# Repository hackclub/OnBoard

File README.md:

# **<h2>Onboard has ended now :/ <br> But much more to come! Stay tuned :). [Sign up here.](https://forms.hackclub.com/t/xtYYcGvNTCus)<h2>**

# OnBoard - Get a $100 grant and make a PCB!

> "I’m so glad that young people can create things like PC boards online. May your creativity have no limits!”
>
> _– [Steve Wozniak](https://en.wikipedia.org/wiki/Steve_Wozniak), Apple co-founder endorsing Hack Club OnBoard_

It's easier than ever for high school students to get involved with programming; all you need is a computing device and internet access. Yet, *it's not the same for hardware*. While PCB fabs have greatly increased the accessibility for professionally done boards, there is still no clear way for high school students to jump in. This is where OnBoard comes in.

---

Every student will receive up to $100 to cover PCB manufacturing costs, and join a community of peers– some more beginner and some more experienced.

## Requirements

Every design/submission needs to meet the following constraints to be approved:

- Unique and open-source design
- Must be orderable on JLCPCB or other [approved vendor](https://github.com/hackclub/OnBoard/blob/main/docs/VENDORS.md)
- Must be in high school or younger[^1][^2][^3] and show proof of school enrollment to submit

[^1]: Home school still counts!
[^2]: If you left high school early you can also submit.
[^3]: If you need help with ideas for proof of age, ask in our Slack and we'll help you out! [here](https://hackclub.com/slack/?event=onboard)

## Getting Started

> You can also go through a video with instructions on how to submit your grant!
>
> 

### Star the repo (Optional)

To follow the repo for updates and show you're participating, click the "star" button on the [`onboard`](https://github.com/hackclub/OnBoard/) repo.

### 1. Join `#electronics` on Slack!

Our [`#electronics`](https://hackclub.slack.com/archives/C0587U78RK4) channel[^4] is where the party is getting started! If you haven't already joined, make sure to add yourself to the channel. And for those who are new to the Hack Club slack, sign up to our community of 13k+ makers through [here](https://hackclub.com/slack/?event=onboard) (don't worry, there isn't an application).

[^4]: This link only works after you've joined the slack. Make sure to get an invite [here](https://hackclub.com/slack/?event=onboard) first.

Perhaps ping a little hello to `@Kevin Yang`?

### 2. Design a Board!

It's design time! If you've done this before, you can skip ahead to step 3. Most people reading this will be new to PCB design, so we've made a simple tutorial on making an example board.

Check out our [PCB tutorials](https://jams.hackclub.com/tag/pcb), where you'll make a design from scratch in a free online editor. This is jumping in the deep end- it won't explain everything, but it will give you a taste of what's possible. By the end you probably won't understand _what_ you did or _why_ you did it, but you will have a working design for a board and you'll know how to **tweak** and **edit** the design to make it your own.

_If you get stuck on these tutorials, or want more example projects to learn from, post in the Slack channel to hear from others going on their journeys._

### 3. Upload to a Vendor and Take a Screenshot

Upload your Gerber files to [JLCPCB.com](https://jlcpcb.com/) and add them to your cart. JLCPCB is the default PCB manufacturer, but you can shop around [^5] if there's a specific one you want to use [^6]. Ensure you complete the checkout process by entering your address and selecting a shipping method. Once completed, take a screenshot with all the final costs and shipping!
> If you're curious what all the settings are about or how to order for assembly, check out our [`ordering_from_JLCPCB.md`](./docs/ordering_from_JLCPCB.md) doc!
> To avoid excess shipping fees or customs, check out [`the Shipping Tips`](./community/shipping.md) doc!

It should look like this:

**Note:** Your screenshot is **VITAL** since your project cannot be approved without it. You'll include the screenshot in your PR later.

[^5]: Don't know which ones you can use? Check out [`VENDORS.md`](./docs/VENDORS.md) for more info!
[^6]: If outside the US you may be charged customs which aren't covered by the grant! Check beforehand.

### 4. Fork!

Fork the [`onboard`](https://github.com/hackclub/OnBoard/) repo! This is the where you'll add your project files and eventually PR from!

### 5. Add Your Design to Your Project Repo

From your fork of `OnBoard`, create a folder with your project name under `OnBoard/projects`. To do this, go to the projects folder and click `Create new file`.

Then in the box labeled `name your file...`, type in `PROJECT_NAME/README.md`. This creates a README file under a folder called named after your project.

After this, copy and paste the contents of [`TEMPLATE.md`](./projects/!Template/TEMPLATE.md?plain=1) into the text editor and fill it out!

Once your done, press the big green `Commit changes` button to save!

With your README filled out, head over to add files to begin uploading your Gerber, design files, and screen shot of vendor approval.

In all, you should have the following files under your project folder:
- [ ] `README.md`: A filled out [`TEMPLATE.md`](./projects/!Template/TEMPLATE.md?plain=1), renamed to `README.md`
- [ ] `cart.png`: A [screenshot](./docs/images/ordering/cart.png) of your order details
- [ ] `gerber.zip`: This should be the file that you send off to the vendor.
- [ ] `schematic.pdf`: Export the schematic from your EDA program as a PDF.
    - Go to "File > Export > PDF" **in EasyEDA's Schematic tab** for this.
- [ ] `src/`: Make a folder called `src` and Whatever format your designer outputs should be included.
    - For **EasyEDA STD**, you need to File > Export > EasyEDA two JSON files - one from the schematic tab and one from the PCB tab.
      - *Optionally*, for EasyEDA STD, export a 3D Model as `.obj` as save it to the `/src` folder 

    - For **KiCad**, read the [Submitting for KiCad](docs/kicad-submission.md), add the `.kicad_pcb`, `.kicad_sch` and `.kicad_pro` files to your `/src` folder.
      - What is **KiCad**? See [KiCad for Beginners](docs/KiCad_Beginner_Guide.md) for a mini tutorial on how to use.
    - Or `design.json`, `design.sch`, `design.brd`, etc for other PCB Editors.

Ensure your file names are exactly the same as above.

Your PR should have a structure like this:

| EasyEDA STD | KiCad |
| ----------- | ----------- |
 | 
----

If you have all the above, you're done with this step!

### 6. Create a PR!

Once you've uploaded your files, you can merge them to the main repo through a pull request! Under the contribute tab of your forked repo, click the big green `Open pull request`.

That will bring you to the main repo, where you'll initiate a pull request. Follow the checklist, we'll then review your PR and you'll be off to the races!

### 7. Get approval and order your board!

Once you submit your PR, it needs two approvals:
- One verifying your high school enrollment documents, from HCB.
- Another one from the engineering team, checking that your design follows the grant requirements.

These reviews typically take 24-48 business hours, and if everything is correct, we'll merge your pull request!

After your pull request gets merged, it can take up to 24 business hours for you to receive an email from HCB with a virtual credit card. Make sure to check your spam folder. Then, you can order your board!

### 8. Ship it!

Post photos of your board in [`#electronics`](https://hackclub.slack.com/archives/C056AMWSFKJ)! We can't wait to see what you make!

## Example Projects

- [PCB Business Card with NFC, "Hackercard"](https://jams.hackclub.com/jam/hacker-card)
- [Build a USB Hub](https://jams.hackclub.com/batch/usb-hub)
- [Make a Digital Level](https://jams.hackclub.com/batch/sparkletilt-pcb)

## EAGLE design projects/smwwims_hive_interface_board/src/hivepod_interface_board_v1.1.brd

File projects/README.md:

---
name: "Daniel Pilkington"
slack_handle: "@Daniel Pilkington"
github_handle: "@danjpilkE"
tutorial: # https://jams.hackclub.com/jam/hacker-card
wokwi: # Link to the Wokwi project if you're submitting for Hacky Holidays
---

# Card

<!-- Describe your board in 2-3 sentences. What are you making? What will it do? -->
A black PCB board with name, github and email
<!-- How much is it going to cost? -->
$21.68
<!-- Tell us a little bit about your design process. What were some challenges? What helped? ***Totally optional*** -->

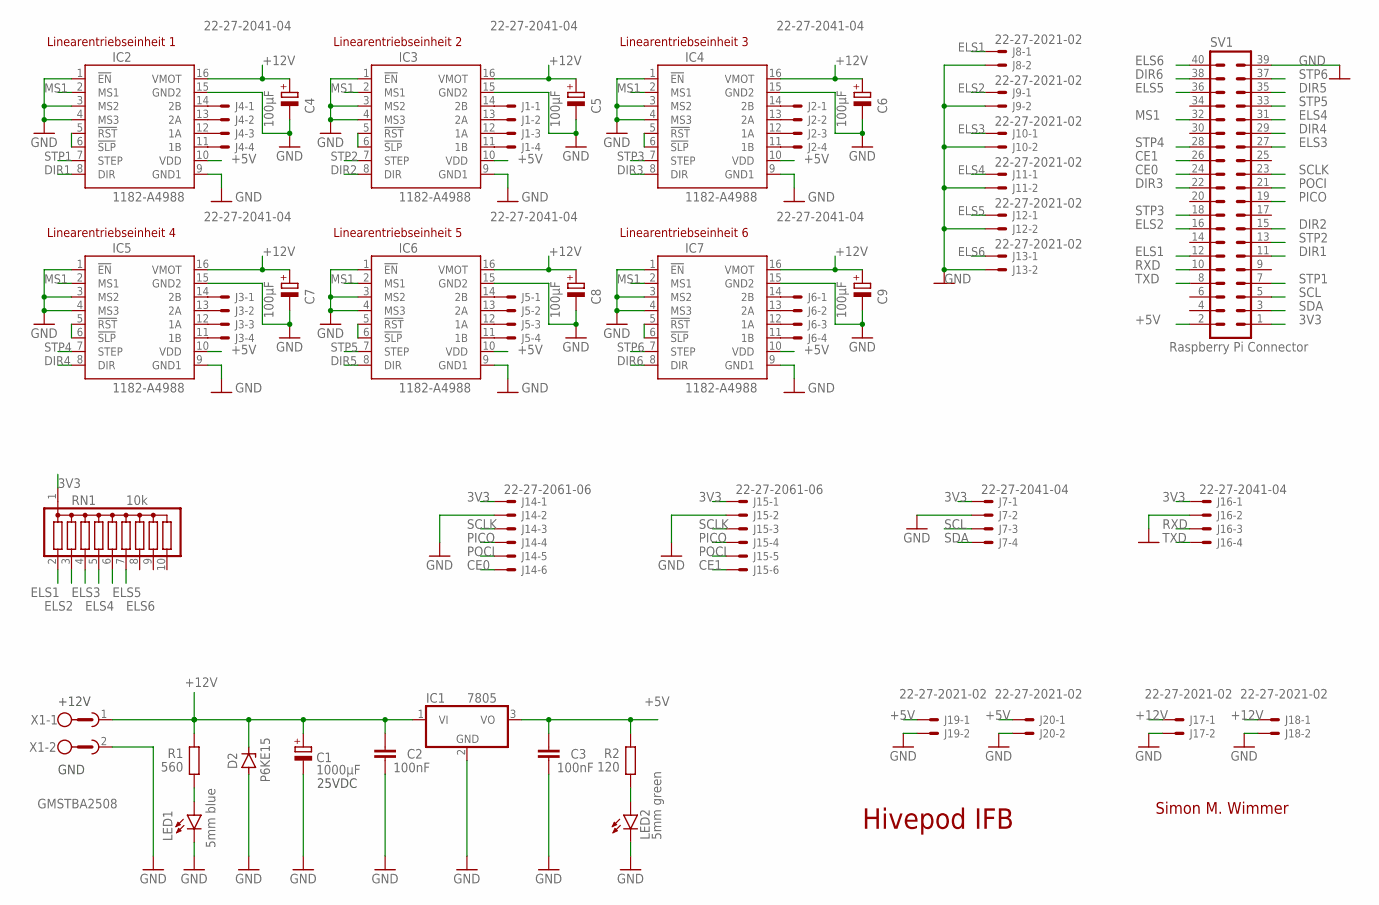
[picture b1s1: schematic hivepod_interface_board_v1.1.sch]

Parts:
C1: 1000µF; E5-10,5
C2, C3: 100nF; C1206
C4, C5, C6, C7, C8, C9: 100µF; E5-6
D2: P6KE15; F126Z12
IC1: 7805; TO220V
IC2, IC3, IC4, IC5, IC6, IC7: 1182-A4988; A4988
J1, J2, J3, J4, J5, J6, J7, J16: 22-27-2041-04; 6410-04
J8, J9, J10, J11, J12, J13, J17, J18, J19, J20: 22-27-2021-02; 6410-02
J14, J15: 22-27-2061-06; 6410-06
LED1: 5mm blue; LED5MM
LED2: 5mm green; LED5MM
R1: 560; R1206
R2: 120; R1206
RN1: 10k; SIL10
SV1: Raspberry Pi Connector; ML40
X1: GMSTBA2508; HOR-2

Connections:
3V3: J7.1, J14.1, J15.1, J16.1, RN1.1, SV1.1
+5V: C3.1, IC1.3 (VO), IC2.10 (VDD), IC3.10 (VDD), IC4.10 (VDD), IC5.10 (VDD), IC6.10 (VDD), IC7.10 (VDD), J19.1, J20.1, R2.2, SV1.2
+12V: C1.+, C2.1, C4.+, C5.+, C6.+, C7.+, C8.+, C9.+, D2.C, IC1.1 (VI), IC2.16 (VMOT), IC3.16 (VMOT), IC4.16 (VMOT), IC5.16 (VMOT), IC6.16 (VMOT), IC7.16 (VMOT), J17.1, J18.1, R1.2, X1.1
CE0: J14.6, SV1.24
CE1: J15.6, SV1.26
DIR1: IC2.8 (DIR), SV1.11
DIR2: IC3.8 (DIR), SV1.15
DIR3: IC4.8 (DIR), SV1.22
DIR4: IC5.8 (DIR), SV1.29
DIR5: IC6.8 (DIR), SV1.35
DIR6: IC7.8 (DIR), SV1.38
ELS1: J8.1, RN1.2, SV1.12
ELS2: J9.1, RN1.3, SV1.16
ELS3: J10.1, RN1.4, SV1.27
ELS4: J11.1, RN1.5, SV1.31
ELS5: J12.1, RN1.6, SV1.36
ELS6: J13.1, RN1.7, SV1.40
GND: C1.-, C2.2, C3.2, C4.-, C5.-, C6.-, C7.-, C8.-, C9.-, D2.A, IC1.2 (GND), IC2.1 (!EN), IC2.3 (MS2), IC2.4 (MS3), IC2.9 (GND1), IC2.15 (GND2), IC3.1 (!EN), IC3.3 (MS2), IC3.4 (MS3), IC3.9 (GND1), IC3.15 (GND2), IC4.1 (!EN), IC4.3 (MS2), IC4.4 (MS3), IC4.9 (GND1), IC4.15 (GND2), IC5.1 (!EN), IC5.3 (MS2), IC5.4 (MS3), IC5.9 (GND1), IC5.15 (GND2), IC6.1 (!EN), IC6.3 (MS2), IC6.4 (MS3), IC6.9 (GND1), IC6.15 (GND2), IC7.1 (!EN), IC7.3 (MS2), IC7.4 (MS3), IC7.9 (GND1), IC7.15 (GND2), J7.2, J8.2, J9.2, J10.2, J11.2, J12.2, J13.2, J14.2, J15.2, J16.2, J17.2, J18.2, J19.2, J20.2, LED1.K (C), LED2.K (C), SV1.39, X1.2
MS1: IC2.2 (MS1), IC3.2 (MS1), IC4.2 (MS1), IC5.2 (MS1), IC6.2 (MS1), IC7.2 (MS1), SV1.32
unnamed: LED1.A, R1.1
unnamed: LED2.A, R2.1
unnamed: IC6.14 (2B), J5.1
unnamed: IC6.13 (2A), J5.2
unnamed: IC6.12 (1A), J5.3
unnamed: IC6.11 (1B), J5.4
unnamed: IC7.14 (2B), J6.1
unnamed: IC7.13 (2A), J6.2
unnamed: IC7.12 (1A), J6.3
unnamed: IC7.11 (1B), J6.4
unnamed: IC3.5 (!RST), IC3.6 (!SLP)
unnamed: IC4.14 (2B), J2.1
unnamed: IC4.13 (2A), J2.2
unnamed: IC4.12 (1A), J2.3
unnamed: IC4.11 (1B), J2.4
unnamed: IC4.5 (!RST), IC4.6 (!SLP)
unnamed: IC5.14 (2B), J3.1
unnamed: IC5.13 (2A), J3.2
unnamed: IC5.12 (1A), J3.3
unnamed: IC5.11 (1B), J3.4
unnamed: IC5.5 (!RST), IC5.6 (!SLP)
unnamed: IC3.14 (2B), J1.1
unnamed: IC3.13 (2A), J1.2
unnamed: IC3.12 (1A), J1.3
unnamed: IC3.11 (1B), J1.4
unnamed: IC6.5 (!RST), IC6.6 (!SLP)
unnamed: IC2.14 (2B), J4.1
unnamed: IC2.13 (2A), J4.2
unnamed: IC2.12 (1A), J4.3
unnamed: IC2.5 (!RST), IC2.6 (!SLP)
unnamed: IC2.11 (1B), J4.4
unnamed: IC7.5 (!RST), IC7.6 (!SLP)
PICO: J14.4, J15.4, SV1.19
POCI: J14.5, J15.5, SV1.21
RXD: J16.3, SV1.10
SCL: J7.3, SV1.5
SCLK: J14.3, J15.3, SV1.23
SDA: J7.4, SV1.3
STP1: IC2.7 (STEP), SV1.7
STP2: IC3.7 (STEP), SV1.13
STP3: IC4.7 (STEP), SV1.18
STP4: IC5.7 (STEP), SV1.28
STP5: IC6.7 (STEP), SV1.33
STP6: IC7.7 (STEP), SV1.37
TXD: J16.4, SV1.8

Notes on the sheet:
+12V
GND
25VDC
Simon M. Wimmer
Hivepod IFB
Linearentriebseinheit 1
Linearentriebseinheit 2
Linearentriebseinheit 3
Linearentriebseinheit 4
Linearentriebseinheit 5
Linearentriebseinheit 6

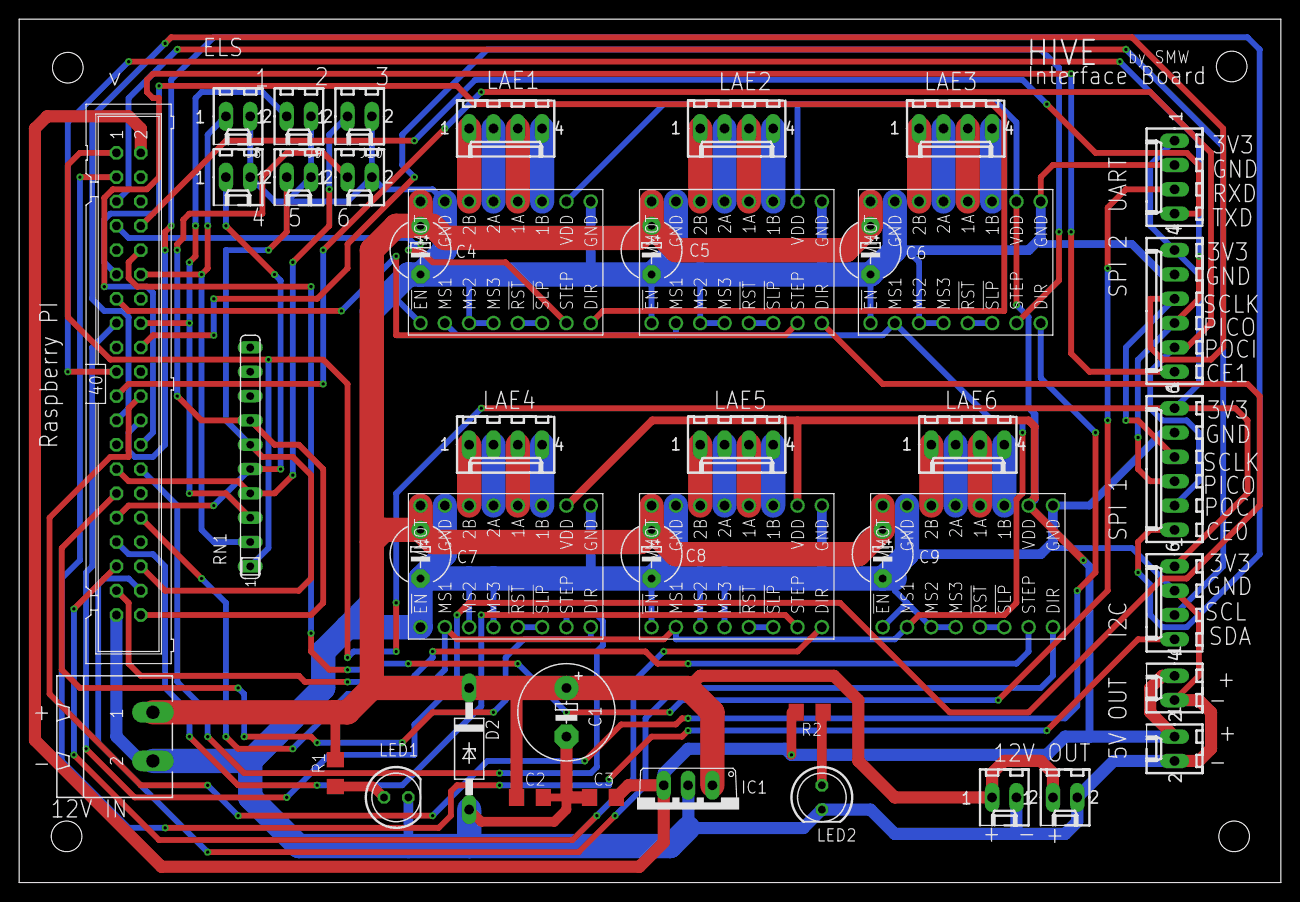
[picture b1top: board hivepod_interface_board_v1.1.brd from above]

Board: 2 copper layers, 131.8 x 90.2 mm, 44 parts (0 on the bottom side), 64 nets.

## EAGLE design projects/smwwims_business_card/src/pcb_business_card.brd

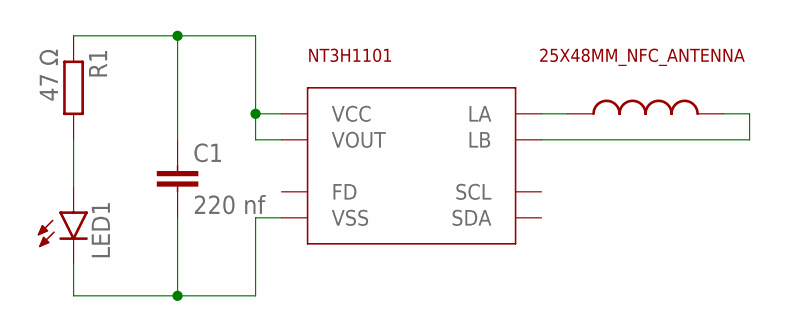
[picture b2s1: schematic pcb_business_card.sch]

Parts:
ANT: 25X48MM_NFC_ANTENNA; 25X48MM_NFC
C1: 220 nf; C0603
LED1: LEDCHIP-LED0805; CHIP-LED0805
NT3H1101: NT3H; XQFN8
R1: 47 Ω; R0603

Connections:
unnamed: ANT.P$2, NT3H1101.LA
unnamed: ANT.P$1, NT3H1101.LB
unnamed: C1.1, NT3H1101.VCC, NT3H1101.VOUT, R1.1
unnamed: LED1.A, R1.2
unnamed: C1.2, LED1.C, NT3H1101.VSS

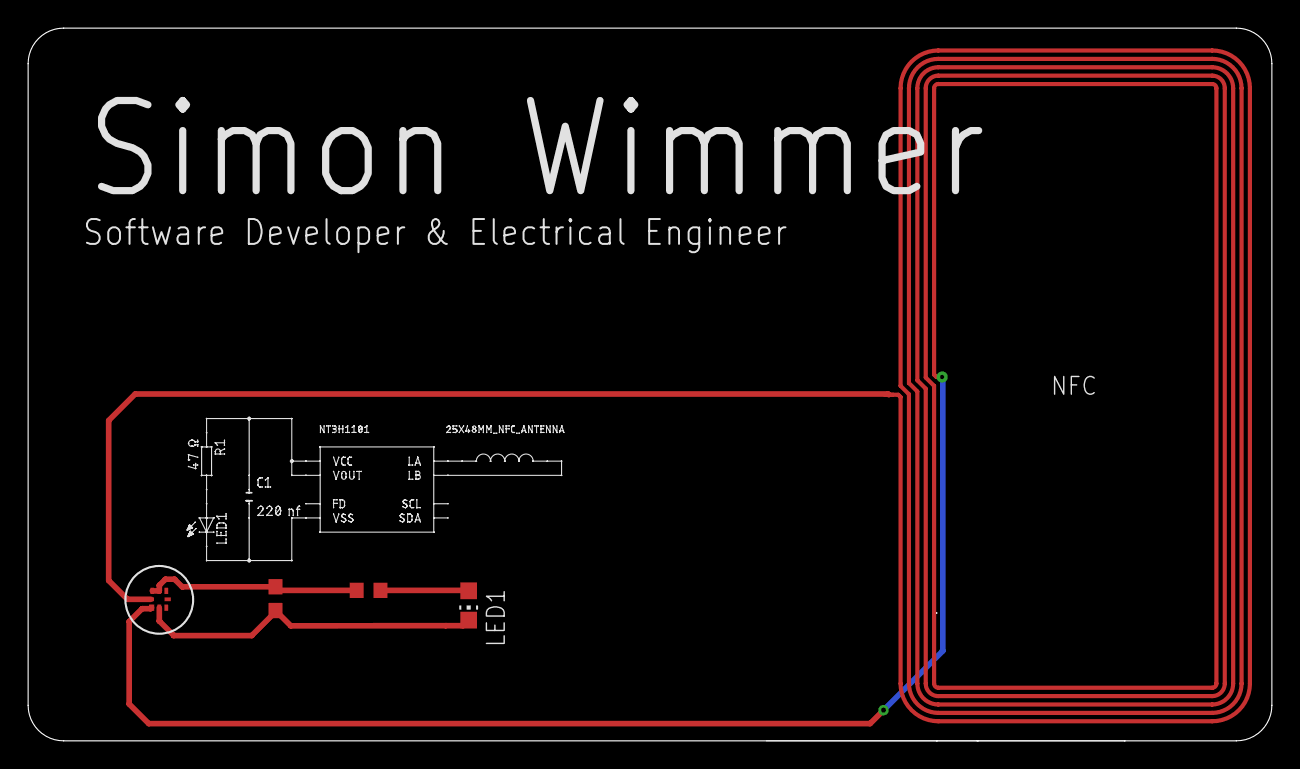
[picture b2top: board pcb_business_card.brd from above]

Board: 2 copper layers, 89.0 x 51.0 mm, 5 parts (0 on the bottom side), 5 nets.

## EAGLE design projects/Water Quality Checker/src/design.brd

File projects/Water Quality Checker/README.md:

---
name: "Shreyans Jain"
slack_handle: "@Shreyans"
github_handle: "@CodeWithShreyans"
---

# Water Quality Checker

<!-- Describe your board in 2-3 sentences. What are you making? What will it do? -->
Building a water quality checker for the Trail which uses TDS, Turbidity and temperature sensors to assess water quality.

<!-- How much is it going to cost? -->
Before the actual sensors and the RPi Pico and the TDS controller board, including shipping it's coming out to $78.54.
However I have almost zero expectation for it to work first try and will likely need to do revisions which idk how I'll pay for.

<!-- Tell us a little bit about your design process. What were some challenges? What helped? ***Totally optional*** -->
Got a lot of help from the Slack. Learnt everything I now know about PCBs during this project.

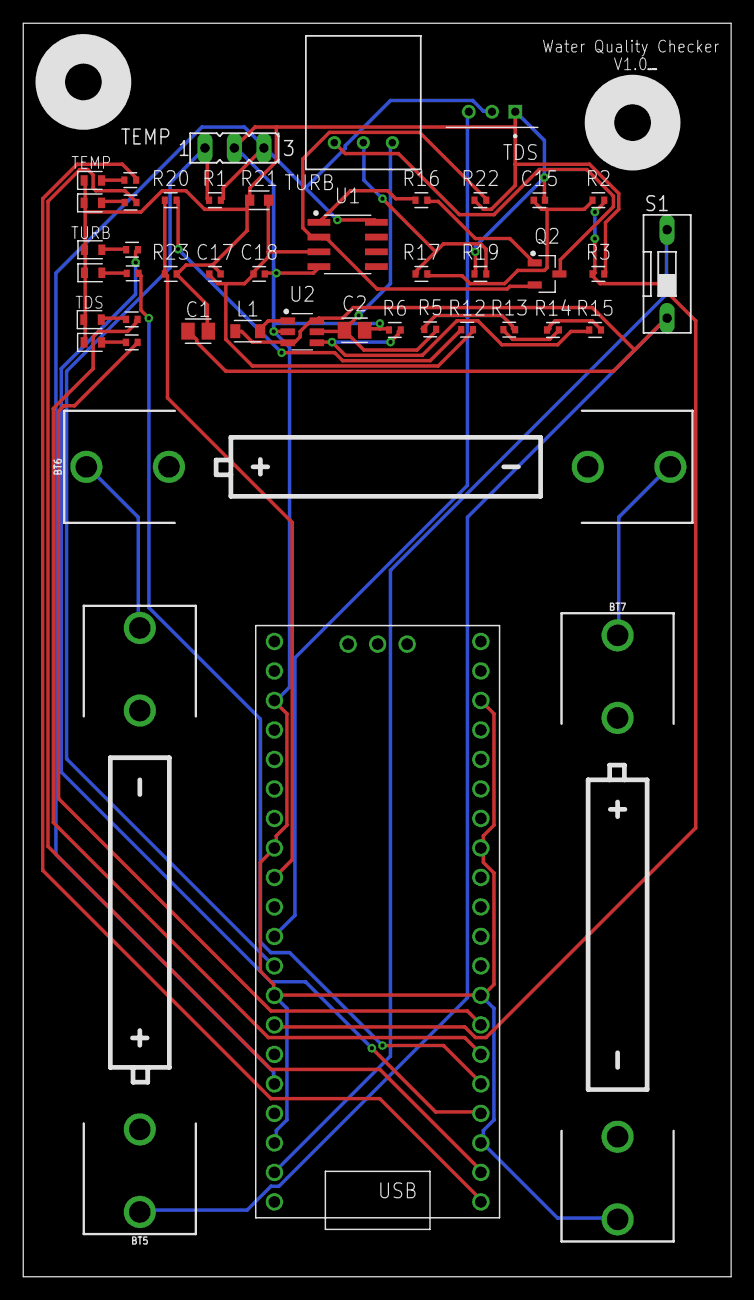
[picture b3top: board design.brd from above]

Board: 2 copper layers, 61.0 x 107.9 mm, 45 parts (0 on the bottom side), 36 nets.

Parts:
BT5, BT6, BT7: BATTERY-AA-KIT
C1, C2: 10µF; CAPC2012X110
C15, C18: 104; CAPC1005X60
C17: 106; CAPC1005X60
L1: 10µH; INDC2009X120
Q2: NPN; SOT95P237X112-3N
R1: 4.7K; RESC1005X40
R2, R3: 20K; RESC1005X40
R4, R7, R8, R9, R10, R11, R16, R23: 150R; RESC1005X40
R5: 1M; RESC1005X40
R6, R13, R14, R15: 200K; RESC1005X40
R12: 200R; RESC1005X40
R17: 100K; RESC1005X40
R19: 3.3K; RESC1005X40
R20: 470R; RESC1005X40
R21: 4.99K; RESC1608X60
R22: 100R; RESC1005X40
S1: DS01; DS-01
TDS: S3B-PH-K-S(LF)(SN)
TDS_G: LED_GREEN; LEDC1608X65N_RND-G
TDS_R: LED_RED; LEDC1608X65N_RND-R
TEMP: FE03-1
TEMP_G: LED_GREEN; LEDC1608X65N_RND-G
TEMP_R: LED_RED; LEDC1608X65N_RND-R
TURB: S3B-XH-A
TURB_G: LED_GREEN; LEDC1608X65N_RND-G
TURB_R: LED_RED; LEDC1608X65N_RND-R
U1: LM358_SOIC; SOIC127P600X175-8N
U2: TPS61073; SOT95P280X110-6N
U$1: RASPBERRY-PI-PICO_TH; FT_RASPBERRY-PI-PICO_TH

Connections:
3V3: R1.2, TDS.2, TEMP.3, U1.8, U$1.36
+5V: C2.1, R5.2, TURB.1, U2.5
GND: BT7.GND@1, C1.2, C2.2, C15.2, C17.2, C18.2, R3.2, R6.1, R19.1, R21.1, R22.1, R23.2, TDS.1, TDS_G.C, TDS_R.C, TEMP.2, TEMP_G.C, TEMP_R.C, TURB_G.C, TURB_R.C, U1.4, U2.2, U$1.3, U$1.8, U$1.13, U$1.18, U$1.23, U$1.28, U$1.33, U$1.38
unnamed: BT5.GND@1, BT6.PWR@1
unnamed: BT6.GND@1, BT7.PWR@1
unnamed: R1.1, TEMP.1, U$1.32
unnamed: R20.1, R23.1, U$1.29
unnamed: R2.2, R3.1, U$1.34
unnamed: TDS.3, U$1.31
unnamed: R4.1, TEMP_R.A
unnamed: R7.1, TEMP_G.A
unnamed: R8.1, TURB_R.A
unnamed: R9.1, TURB_G.A
unnamed: R11.1, TDS_G.A
unnamed: R10.2, U$1.6
unnamed: S1.2, U$1.39
unnamed: L1.2, U2.1
unnamed: R4.2, U$1.1
unnamed: R7.2, U$1.2
unnamed: R8.2, U$1.4
unnamed: R9.2, U$1.5
unnamed: R10.1, TDS_R.A
unnamed: R11.2, U$1.7
unnamed: R12.1, R20.2
unnamed: R5.1, R13.2
unnamed: R13.1, R14.2
unnamed: R14.1, R15.2
unnamed: R6.2, R15.1, U2.4
unnamed: C17.1, C18.1, R12.2, R21.2, U1.3
unnamed: R16.1, U1.1
unnamed: Q2.1, R16.2
unnamed: Q2.2, R22.2, U1.2
unnamed: Q2.3, TURB.3
unnamed: R17.1, R19.2, TURB.2
PT_OUT: C15.1, R2.1, R17.2
VBAT: BT5.PWR@1, C1.1, L1.1, S1.1, U2.3, U2.6

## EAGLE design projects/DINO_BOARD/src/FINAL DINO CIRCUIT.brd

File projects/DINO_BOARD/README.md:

---
name: Valeria De Alba
slack_handle: "@Valeria"
github_handle: "@vale217"
---

# DINO BOARD

<!-- Describe your board in 2-3 sentences. What are you making? What will it do? -->

My board is a dinosaur modeled after my little cousin's drawing of one (his favorite creature) that will have LED lights as its eye as well as along his back to give the look of small spikes.
It will be turned into a clip and gifted to my cousin so he can put it on his backpack.

<!-- How much is it going to cost? -->

The board will cost: $96.83

<!-- Tell us a little bit about your design process. What were some challenges? What helped? ***Totally optional*** -->

My design process was fairly straightforward.
I am a beginner and it was my first time making a PCB board so I designed the outline on rhino and then worked on the rest on eagle. 
A challenge I encountered was that I changed my mind about a design that I liked but that would complicate things with all the shapes and cut-outs.
For me, listening to music while working through this project helped a lot, as well as just looking things up on Google when needed.

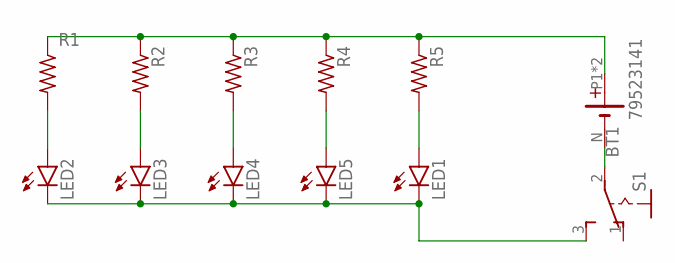
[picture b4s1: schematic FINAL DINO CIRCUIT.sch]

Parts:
BT1: 79523141
LED1, LED2, LED3, LED4, LED5: LED3MM
R1, R2, R3, R4, R5: R-US_0204/5; 0204/5
S1: M251

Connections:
unnamed: LED2.A, R1.2
unnamed: LED1.K (C), LED2.K (C), LED3.K (C), LED4.K (C), LED5.K (C), S1.3 (S)
unnamed: BT1.P1 (+), BT1.P2 (+), R1.1, R2.1, R3.1, R4.1, R5.1
unnamed: LED3.A, R2.2
unnamed: LED4.A, R3.2
unnamed: LED5.A, R4.2
unnamed: LED1.A, R5.2
unnamed: BT1.N (-), S1.2

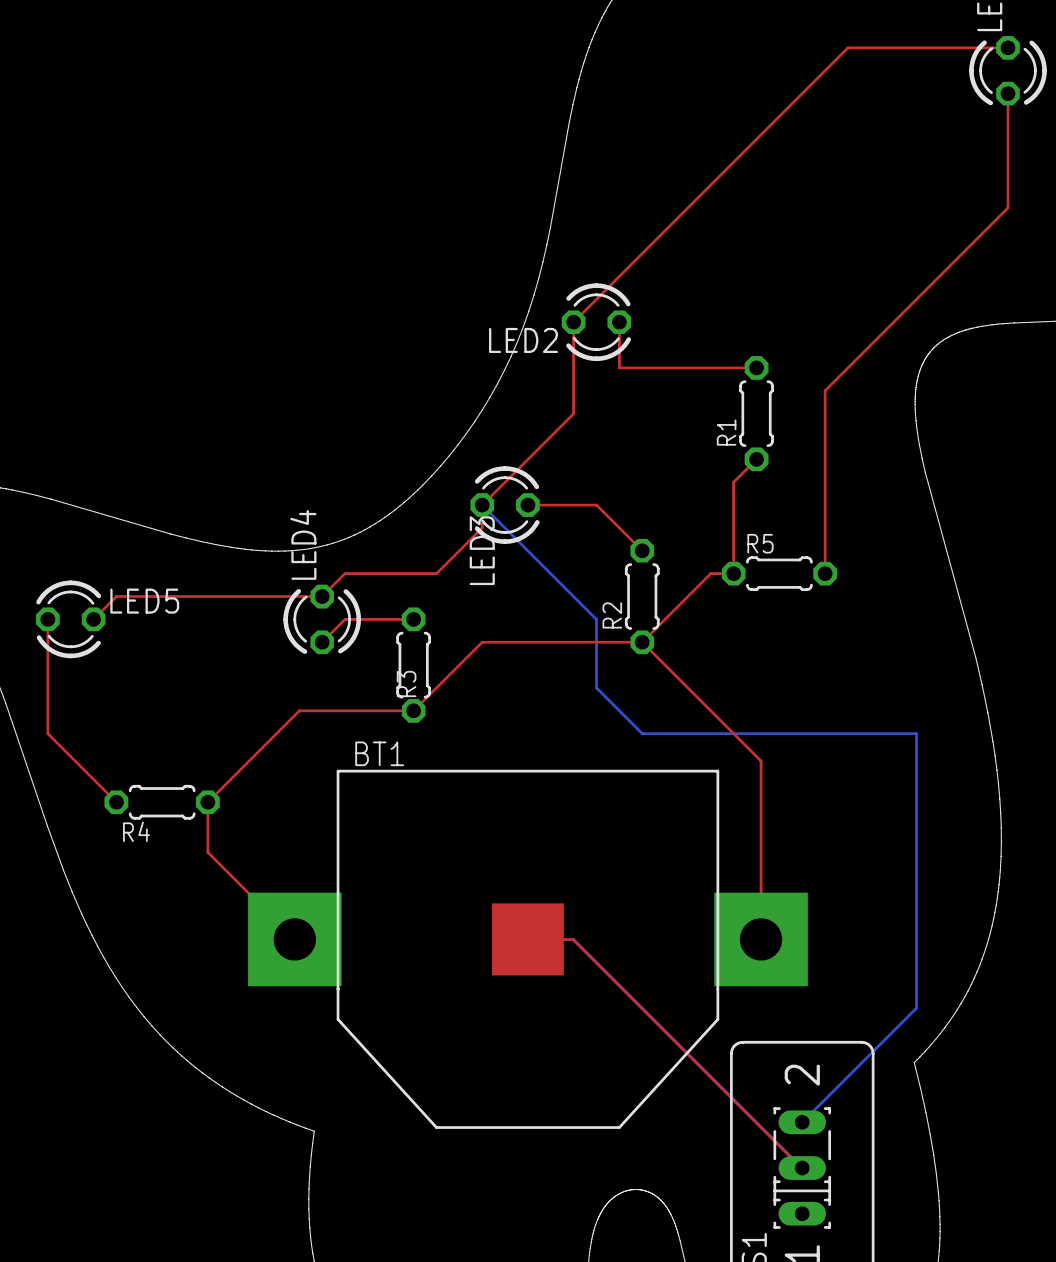
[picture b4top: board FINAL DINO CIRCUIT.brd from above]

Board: 2 copper layers, 12 parts (0 on the bottom side), 8 nets.

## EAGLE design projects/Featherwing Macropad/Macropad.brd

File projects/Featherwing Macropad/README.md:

---
name: "Leo Ma"
slack_handle: "@leo (Leo M)"
github_handle: "@Leo32345"
project: "Featherwing Macropad"

---

# Featherwing Macropad
## Summary
##### I am going to make a 4-key Cherry MX macropad that will be powered by an Adafruit Featherwing. There will also be a small monochrome OLED display.

## Plan
##### 3 PCB boards from OSH Park will cost $30.85. I will buy the Adafruit Featherwing, battery, battery charger, OLED display, Cherry MX, and the keycaps using my own money. I plan to assemble/solder these myself.

## Design
##### I designed using Autodesk Eagle and I somewhat followed [this tutorial to design it](https://blog.adafruit.com/2016/12/17/layer-by-layer-cherry-mx-gamepad-in-eagle-cad/) and I will use [this other tutorial to help me assemble it](https://learn.adafruit.com/custom-wireless-bluetooth-cherry-mx-gamepad/overview).

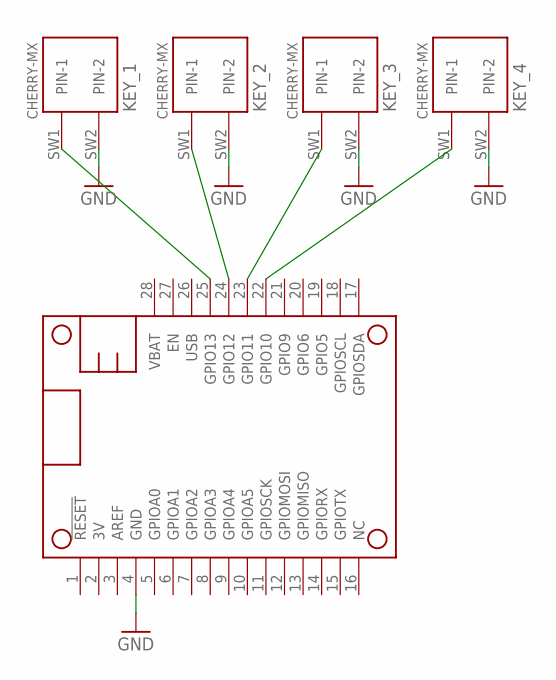
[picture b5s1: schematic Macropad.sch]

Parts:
KEY_1, KEY_2, KEY_3, KEY_4: CHERRY-MX
MS1: FEATHERWING_NODIM; FEATHERWING_DIM

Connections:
GND: KEY_1.SW2 (PIN-2), KEY_2.SW2 (PIN-2), KEY_3.SW2 (PIN-2), KEY_4.SW2 (PIN-2), MS1.4 (GND)
unnamed: KEY_1.SW1 (PIN-1), MS1.25 (GPIO13)
unnamed: KEY_2.SW1 (PIN-1), MS1.24 (GPIO12)
unnamed: KEY_3.SW1 (PIN-1), MS1.23 (GPIO11)
unnamed: KEY_4.SW1 (PIN-1), MS1.22 (GPIO10)

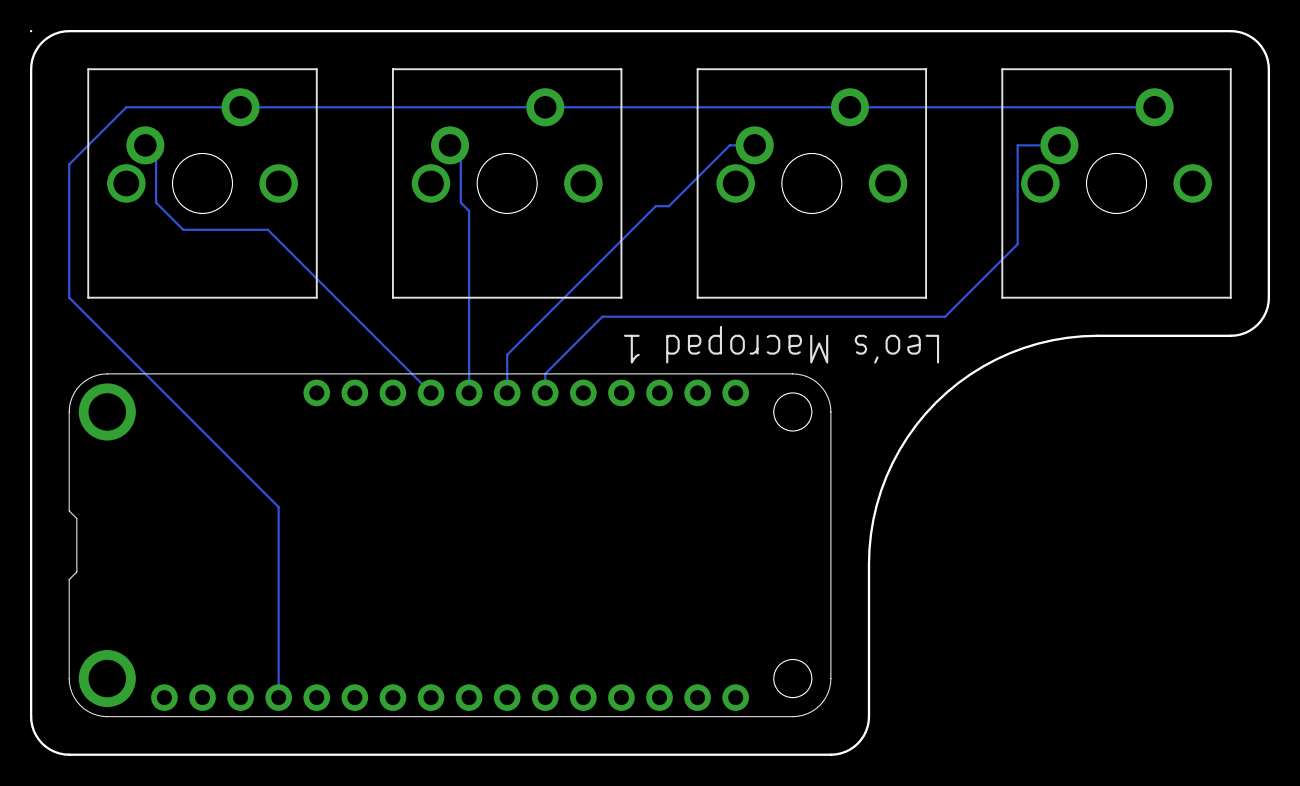
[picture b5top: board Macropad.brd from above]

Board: 2 copper layers, 82.5 x 48.3 mm, 5 parts (0 on the bottom side), 5 nets.

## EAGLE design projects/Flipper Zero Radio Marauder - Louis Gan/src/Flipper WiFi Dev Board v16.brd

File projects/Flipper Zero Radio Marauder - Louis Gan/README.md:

---
name: "Louis Gan"
slack_handle: "@louisgan"
github_handle: "@thelouisgan"
---

# Flipper Zero Radio Marauder

<!-- Describe your board in 2-3 sentences. What are you making? What will it do? -->
## Summary
##### This custom designed Flipper Zero expansion board is a shield for an ESP-32 WiFi microcontroller and NRF24 2.4GHz radio module. It enables multiple addons to enhance my Flipper Zero's functionality in one board

<!-- How much is it going to cost? -->
##### Since it is just a simple shield, the PCB itself will only cost $3.10 for the board, and $10.80 for shipping

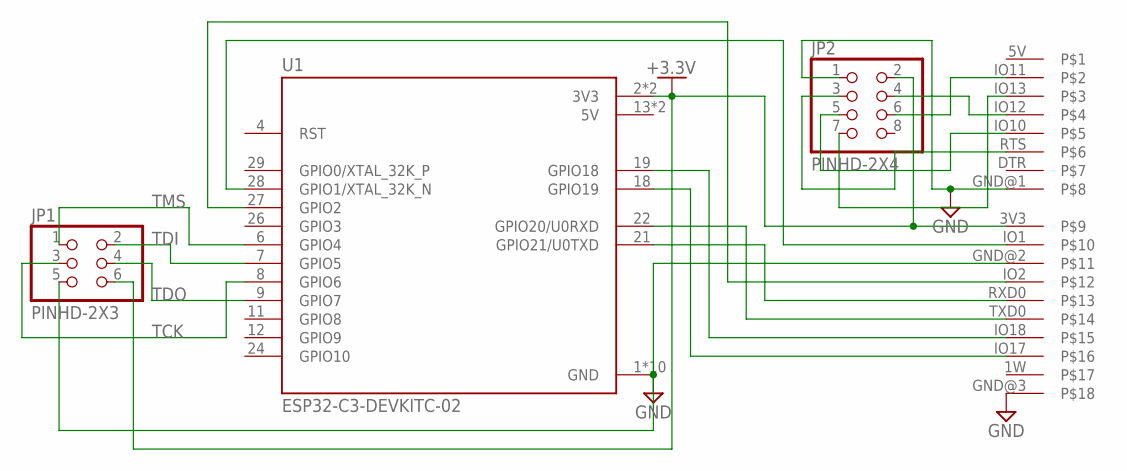
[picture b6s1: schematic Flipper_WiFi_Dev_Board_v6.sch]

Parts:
JP1: PINHD-2X3; 2X03
JP2: PINHD-2X4; 2X04
U1: ESP32-C3-DEVKITC-02; XCVR_ESP32-C3-DEVKITC-02
U$1: FLIPPER_DEVBOARD; FLIPPER

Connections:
5V: U1.13 (5V), U1.14 (5V)
+3.3V: JP1.6, JP2.2, U1.2 (3V3), U1.3 (3V3), U$1.3V3
GND: JP1.5, JP2.1, U1.1 (GND), U1.5 (GND), U1.10 (GND), U1.15 (GND), U1.16 (GND), U1.17 (GND), U1.20 (GND), U1.23 (GND), U1.25 (GND), U1.30 (GND), U$1.GND@1, U$1.GND@2, U$1.GND@3
unnamed: U1.21 (GPIO21/U0TXD), U$1.RXD0
unnamed: U1.22 (GPIO20/U0RXD), U$1.TXD0
unnamed: U1.28 (GPIO1/XTAL_32K_N), U$1.IO1
unnamed: U1.27 (GPIO2), U$1.IO2
unnamed: U1.19 (GPIO18), U$1.IO18
unnamed: U1.18 (GPIO19), U$1.IO17
unnamed: JP2.3, U$1.RTS
unnamed: JP2.4, U$1.IO12
unnamed: JP2.5, U$1.IO10
unnamed: JP2.6, U$1.IO11
unnamed: JP2.7, U$1.IO13
TCK: JP1.3, U1.8 (GPIO6)
TDI: JP1.2, U1.7 (GPIO5)
TDO: JP1.4, U1.9 (GPIO7)
TMS: JP1.1, U1.6 (GPIO4)

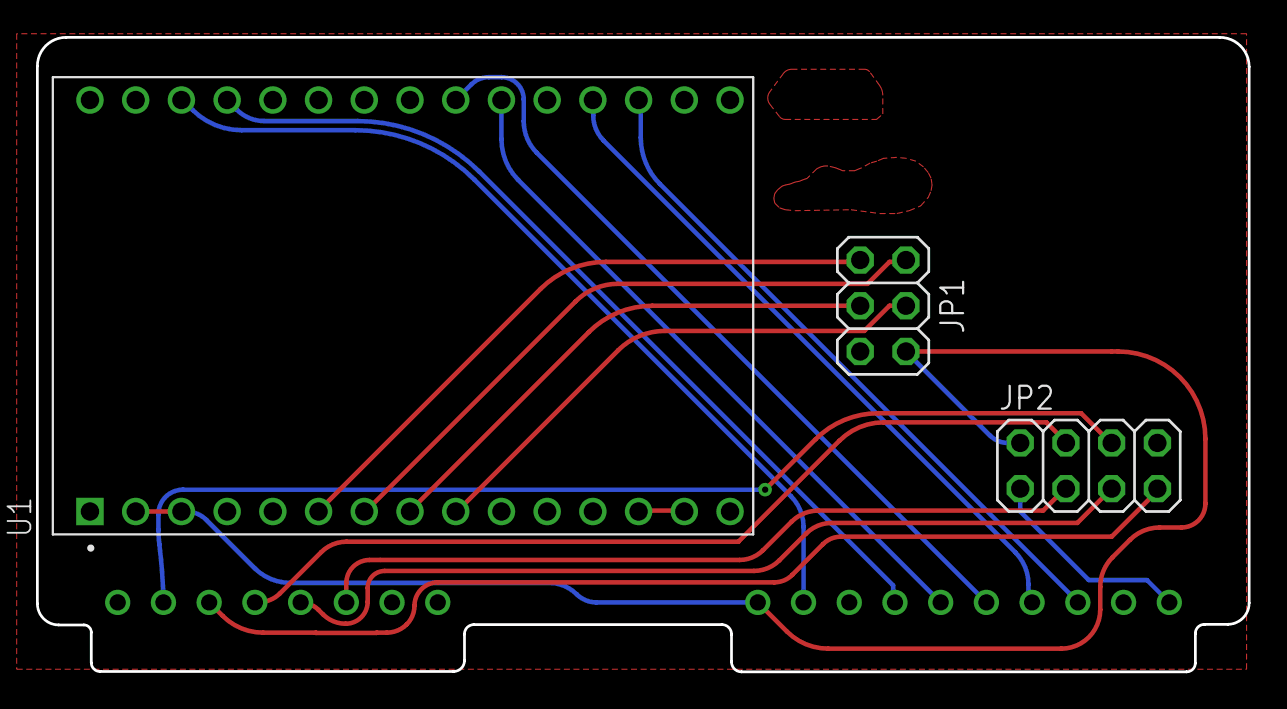
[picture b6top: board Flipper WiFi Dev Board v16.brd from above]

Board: 2 copper layers, 67.3 x 35.2 mm, 4 parts (0 on the bottom side), 18 nets.

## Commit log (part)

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2025-04-19 Horizon_Orbit (#1697)
    * Create README.md
    * Add files via upload
    * Create a
    * Add files via upload
    * Delete projects/Horizon_Orbit/src/a
2025-04-19 add toby's raver
2025-04-19 Update existing tobydio board (#1696)
    * update tobydio board errors
    * update tobydio board
2025-04-19 ControlPad (#1693)
    * Create README.md
    * Update README.md
    * Update README.md
    * Update README.md
    * Add files via upload
    * Rename Gerber_ControlPad.zip to gerber.zip
2025-04-19 Rename projects/Yoav_Mlotok_Business_Card/yoav-mlotok-card.epro to projects/Yoav_Mlotok_Business_Card/src/project.epro
2025-04-20 Add uSDReader
2025-04-20 Owais_school_card (#1687)
    * Create owais-school-thingy
    * Create README.md
    * Update README.md
    * Add files via upload
    * Create README.md
    * Add files via upload
2025-04-20 feat: update megapad design and schematic
2025-04-20 add my own project
2025-04-20 Add schematic
2025-04-20 Add files via upload
    this is a project to use the rest of the 5$ in my onboard hcb card
2025-04-20 create src/
2025-04-20 Add kicad editor files
2025-04-20 add cart images
2025-04-20 update costs
2025-04-20 Dav-Hub (#1699)
    * Create readme.md
    * Add files via upload
    * Rename readme.md to README.md
    * Add files via upload
    * Update README.md
    ---------
2025-04-20 Add uSDReader (#1702)
2025-04-20 Add Ayaan's NFC Tag (#1700)
    * Create README.md
    * Update README.md
    * Update README.md
    * Add files via upload
    * Add files via upload
    * Update README.md
2025-04-20 SaltyMold-Card (#1546)
    * Create README.md
    * Create README.md
    * Add files via upload
    * Delete projects/NFC SaltyMold directory
    * Update README.md
    * Rename commande.png to cart.png
2025-04-20 change to minimum order size
2025-04-20 update prices
2025-04-20 added (hopefully) all required files
2025-04-20 Created Yoav Mlotok's project (#1701)
    * Create README.md
    * Add files via upload
    * Add files via upload
    * Add files via upload
    * Rename projects/Yoav_Mlotok_Business_Card/yoav-mlotok-card.epro to projects/Yoav_Mlotok_Business_Card/src/project.epro
2025-04-20 Create hello
2025-04-20 Rename Screenshot 2025-04-20 193452.png to cart.png
2025-04-21 protoboard (#1681)
    * Create readme.md
    * Add files via upload
    * Delete projects/protoboard/gerber.zip
    * Add files via upload
    * Delete projects/protoboard/src/pcb.json
    * Add files via upload
2025-04-21 Onboard Grant (#1707)
    * Create readme.md
    * Add files via upload
2025-04-21 title (#1708)
    * Create readme.md
    * Add files via upload
2025-04-21 Andreas-usb (#1691)
    * Create readme.md
    * Add files via upload
    * Rename readme.md to README.md
    * Delete projects/Usb-Hub/src/PCB.json
    * Delete projects/Usb-Hub/schematic.pdf
    * Delete projects/Usb-Hub/gerber.zip
2025-04-21 Add PCB art to use the rest of 5$ in my onboard hcb (#1703)
    * Add files via upload
    * Delete projects/reversible split keyboard/price.png
    * Delete projects/reversible split keyboard/Gerbers.zip
    * Add files via upload
    * Add files via upload
    * Delete projects/reversible split keyboard/reversible.kicad_pcb
2025-04-22 EEPROM Programmer (#1709)
    * Create README.md
    * Update README.md
    * Add files via upload
    * Add files via upload
    * Add files via upload
    * Add files via upload
2025-04-22 Rename Schematic_learningpcb_2025-04-21.pdf to schematic.pdf
2025-04-22 Rename image_2025-04-21_222704961.png to cart.png
2025-04-22 Rename Gerber_learningpcb_PCB_learningpcb_2025-04-21.zip to gerber.zip
2025-04-22 Rename gerber (2).zip to gerber.zip
2025-04-22 Rename schematic (1).pdf to schematic.pdf
2025-04-22 USB-C (#1712)
    * Create readme.md
    * Add files via upload
    * Rename gerber (2).zip to gerber.zip
    * Rename schematic (1).pdf to schematic.pdf
2025-04-23 added src
2025-04-23 added config.yaml
2025-04-23 SD-Card (#1711)
    * Create readme.md
    * Add files via upload
    * Update and rename Pcb.json to Pcb.json
    * Update and rename Schematic.json to Schematic.json
2025-04-23 Rename Hackpad.pdf to schematic.pdf
2025-04-23 added files
2025-04-23 [No grant needed] Update megapad schematic and gerber files (#1716)
2025-04-23 Rename cap.pdf to schematic.pdf
2025-04-23 Rename gerber (3).zip to gerber.zip
2025-04-23 Rename Schematic_fuelsensor_2025-04-23.pdf to schematic.pdf
2025-04-23 Add Calculusulator (#1689)
    * Create README.md
    * Update README.md
    * Update README.md
    * Create placeholder
    * Delete projects/Calculusulator/src/placeholder
    * Create placeholder
2025-04-23 yapyapyapyap
2025-04-23 very skibidi
2025-04-24 grant pls!!
2025-04-25 Update VENDORS.md added elecrow pcba service (#1652)
2025-04-25 tanisha_in_space (#1722)
    * Create readme.md
    * Add files via upload
    * Add files via upload
    * Delete projects/tanisha_in_space/cart.png.png
    * Add files via upload
2025-04-25 fuel_sensor (#1720)
    * Create readme.md
    * Add files via upload
    * Rename gerber (3).zip to gerber.zip
    * Update and rename projects/fuel_sensor/PCB_PCB_fuelsensor_2025-04-23.json to projects/fuel_sensor/src/PCB.json
    * Update and rename projects/fuel_sensor/SCH_fuelsensor_2025-04-23.json to projects/fuel_sensor/src/SCH.json
    * Rename Schematic_fuelsensor_2025-04-23.pdf to schematic.pdf
2025-04-25 skib (#1721)
    * yapyapyapyap
    * very skibidi
2025-04-25 MemoryBoard (#1718)
    * Create readme.md
    * Add files via upload
2025-04-25 adding project QPD_AMPLIFIER (#1705)
    * Create README.md
    * Update README.md
    * Update README.md
    * added (hopefully) all required files
2025-04-25 Onboard PCB macroboard (#1719)
    * Create readme.md
    * Add files via upload
2025-04-25 Rename projects/gerber.zip to projects/andreascard/gerber.zip
2025-04-25 Rename projects/schematic.pdf to projects/andreascard/schematic.pdf
2025-04-25 Rename projects/image_2025-04-23_170456454.png to projects/andreascard/cart.png
2025-04-25 Rename Gerber_claprelay_pcb_2025-04-26.zip to gerber.zip
2025-04-25 Rename image_2025-04-26_003502681.png to cart.png
2025-04-25 Rename Schematic_claprelay_2025-04-26.pdf to schematic.pdf
2025-04-26 Lucy's PCB is HOT, HOT, HOT!
2025-04-27 Rename odyssey.gbr.zip to gerber.zip
2025-04-27 Rename odyssey.pdf to schematic.pdf
2025-04-27 Hewis_CArd (#1723)
    * Create hello
    * Add files via upload
    * Create readme.md
    * Delete projects/hewis_hacker_card/src/hello
    * Add files via upload
    * Rename Screenshot 2025-04-20 193452.png to cart.png
2025-04-27 odysseymain (#1728)
    * Create README.md
    * Update README.md
    * Add files via upload
    * Create test.md
    * Add files via upload
    * Rename odyssey.gbr.zip to gerber.zip
2025-04-27 Lucy's PCB (#1727)
    Lucy's PCB is HOT, HOT, HOT!
2025-04-27 add clap relay project (#1726)
    * Create readme.md
    * Add files via upload
    * Rename Gerber_claprelay_pcb_2025-04-26.zip to gerber.zip
    * Rename image_2025-04-26_003502681.png to cart.png
    * Rename Schematic_claprelay_2025-04-26.pdf to schematic.pdf
    * Update and rename projects/claprelaymodule/SCH_claprelay_2025-04-26.json to projects/claprelaymodule/src/sch.json
2025-04-27 PLS add trufflesyt/onboard (#1725)
    grant pls!!
2025-04-27 Pull request for Layan's DJ Controller (#1715)
    * Create README.md
    * Add files via upload
    * Rename Hackpad.pdf to schematic.pdf
    * added files
2025-04-27 Create dummy
2025-04-27 Max's Charlieplexed Matrix! (#1704)
    * add my own project
    * Add schematic
    * create src/
    * Add kicad editor files
    * add cart images
    * update costs
2025-04-27 Rename {BD718A0A-87D1-4BF1-A4F7-5F7D5730A019}.png to cart
2025-04-27 Rename cart to cart.png
2025-04-27 Rename Gerber.zip to gerber.zip
2025-04-27 Create
2025-04-27 Create file
2025-04-28 Rename Screenshot 2025-04-28 185815.png to cart.png
2025-04-29 Rename projects/PCB-fethead/cart.png to projects/PCB-fethead/src/cart.png
2025-04-29 Rename projects/PCB-fethead/src/cart.png to projects/PCB-fethead/cart.png
2025-04-29 e (#1724)
2025-05-02 Create src
2025-05-02 Rename Schematic.pdf to schematic.pdf
2025-05-03 Create e
2025-05-03 Rename JLCPCB.png to cart.png
2025-05-03 added end
2025-05-03 heading h2
2025-05-03 Onboard ended (#1738)
    * RGB_C
    * Delete projects/rgb_strip_controller/src/fp-info-cache
    * Add files via upload
    * Update README.md
    * Update README.md
    * added end
2025-05-03 fix (#1739)
    * RGB_C
    * Delete projects/rgb_strip_controller/src/fp-info-cache
    * Add files via upload
    * Update README.md
    * Update README.md
    * added end
2025-05-03 fix (#1739) (#1740)
    * RGB_C
    * Delete projects/rgb_strip_controller/src/fp-info-cache
    * Add files via upload
    * Update README.md
    * Update README.md
    * added end
2025-05-03 Rename projects/a3acx_hacker_card/PCB_NFC Card.json to projects/a3acx_hacker_card/src/pcb.json
2025-05-03 Rename projects/a3acx_hacker_card/NFC Card.json to projects/a3acx_hacker_card/src/schematic.json
2025-05-04 Add Icepi Zero
2025-05-05 Create README.md (#1745)
    * Create README.md
    * Add files via upload
    * Create src
    * Delete projects/Neha NFC Card/src
    * Create .gitkeep
    * Add files via upload
2025-05-05 ODOMETER!!!!!!!! (#1733)
    * Create README.md
    * Update README.md
    * Add files via upload
    * Add files via upload
    * Add files via upload
    * Add files via upload
2025-05-05 Added src folder
2025-05-06 Smart Ring added
2025-05-06 testing
2025-05-06 Business Card Thingy (#1729)
    * Create README.md
    * Update README.md
    * Add files via upload
    * Create dummy
    * Add files via upload
    * Update README.md
2025-05-08 Add all files related to smart-ring
2025-05-08 Rename cart.png.png to cart.png
2025-05-08 Smart Ring (#1748)
    * Add all files related to smart-ring
    * Rename cart.png.png to cart.png
2025-05-09 Rename cart.PNG to cart.png
2025-05-09 Rename gerber.zip.zip to gerber.zip
2025-05-10 Herculus Bat C HUB (#1731)
    * Create readme.md
    * Create hello
    * Add files via upload
    * Rename Screenshot 2025-04-28 185815.png to cart.png
    * Add files via upload
    * Add files via upload
2025-05-10 Miku NFC Key Chain (#1742)
    * Create README.md
    * Add files via upload
    * Rename Capture.PNG to cart.png
    * Rename Gerber_Hacker-Card_PCB_Hacker-Card_2024-09-23.zip to gerber.zip
    * Add files via upload
    * Rename Schematic_Hacker-Card_2024-09-23.pdf to schematic.pdf
2025-05-15 Create Abhinav's Business Card
2025-05-15 Rename Abhinav Schematic May 15 2025.pdf to schematic.pdf
2025-05-16 Rename projects/Abhinav's PCB Card/Abhinav Schematic May 15 2025.json to projects/Abhinav's PCB Card/src/schematic.json
2025-05-16 Rename Abhinav Schematic May 15 2025 (1).json to pcb.json
2025-05-16 Rename gerber-2.zip to gerber.zip
2025-05-17 Create projects123
2025-05-17 Create conors nfc card
2025-05-17 Rename conors nfc card to conors-nfc-card.md
2025-05-24 added card.png
2025-05-25 Home Assistant Control pad
2025-05-25 cart
2025-05-25 fix folder name
2025-05-27 submit esp-streamer (#1730)
    * Create README.md
    * Add files via upload
    * Create
    * Delete projects/esp-streamer/src
    * Create file
    * Add files via upload
2025-05-27 Ultra USB Hub (#1735)
    * Create README.md
    * Add files via upload
    * Add files via upload
    * Create useless.txt
    * Add files via upload
    * Delete projects/ultra_usb_hub/schematic.json
2025-05-27 Add files via upload
    all the stuff
2025-05-27 Rename BOM_cool_thing_2025-05-27.csv to BOM.csv
2025-05-27 Rename PickAndPlace_PCB_cool_thing_2025-05-27.csv to PickAndPlace.csv
2025-05-27 Rename Schematic_cool_thing_2025-05-27.pdf to Schematic.pdf
2025-05-27 Rename Gerber_cool_thing_PCB_cool_thing_2025-05-27.zip to gerber.zip
2025-05-27 easy eda files😔
2025-05-28 final commit
2025-05-29 Rename Screenshot 2025-05-28 141100.png to cart.png

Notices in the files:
parts and their libraries:
SparkFun-Batteries: Licensing: Creative Commons ShareAlike 4.0 International - https://creativecommons.org/licenses/by-sa/4.0
